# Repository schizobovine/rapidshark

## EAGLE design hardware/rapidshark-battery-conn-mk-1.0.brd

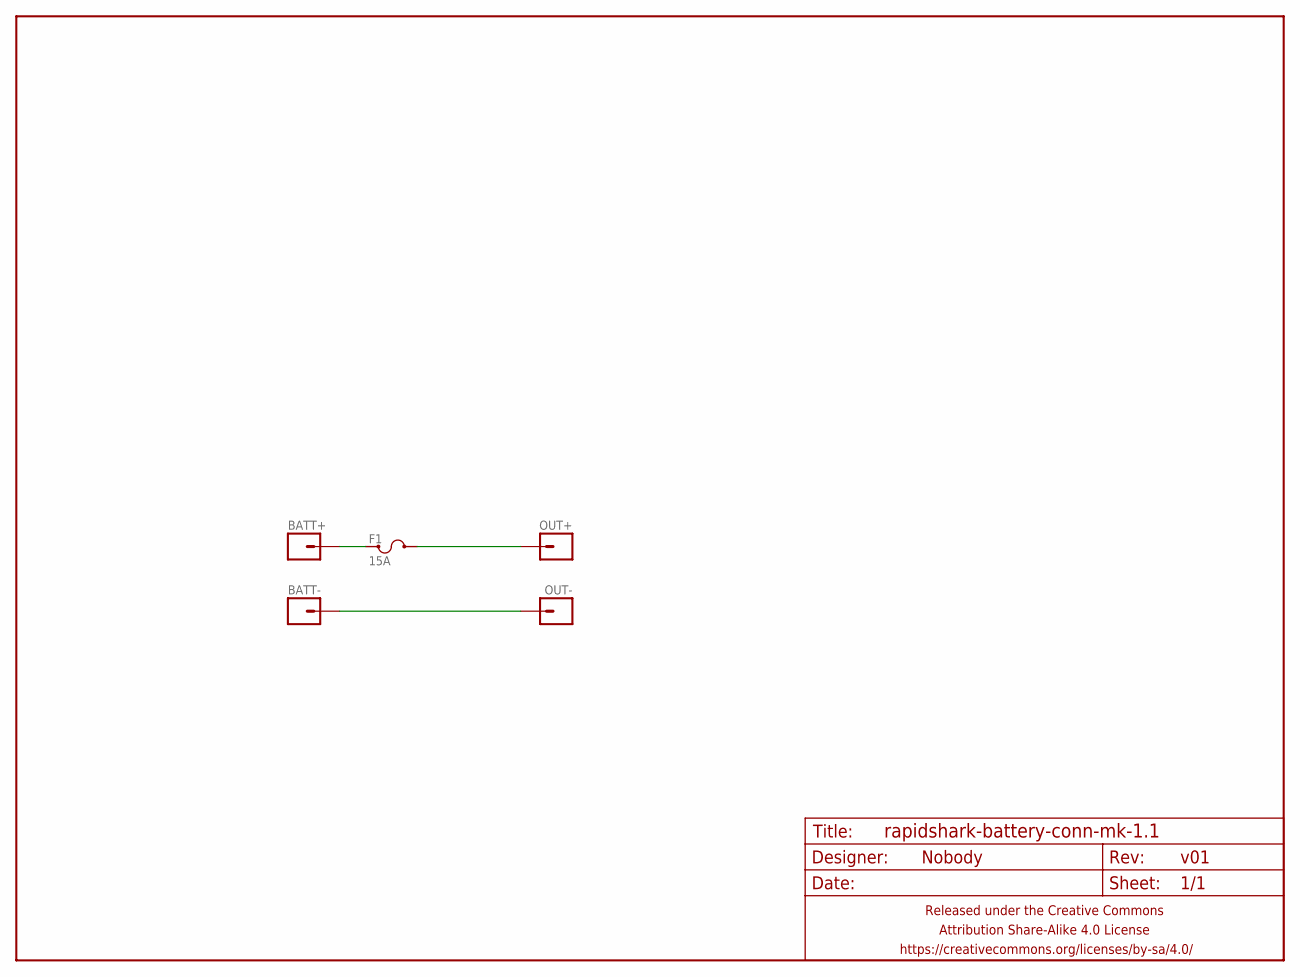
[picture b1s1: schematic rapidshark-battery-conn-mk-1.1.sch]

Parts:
BATT+: M01PTH-2.3MM; 1X01-2.3MM
BATT-: M01PTH-2.3MM; 1X01-2.3MM
F1: 15A; KEYSTONE-MINI-AUTO-FUSE-HOLDER
FRAME1: FRAME-LETTERNO_PACKAGE; DUMMY
OUT+: M0112AWG; 1X01-12AWG
OUT-: M0112AWG; 1X01-12AWG

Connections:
BATT+: BATT+.1, F1.P1@1 (1), F1.P1@2 (1)
BATT-: BATT-.1, OUT-.1
OUT+: F1.P2@1 (2), F1.P2@2 (2), OUT+.1

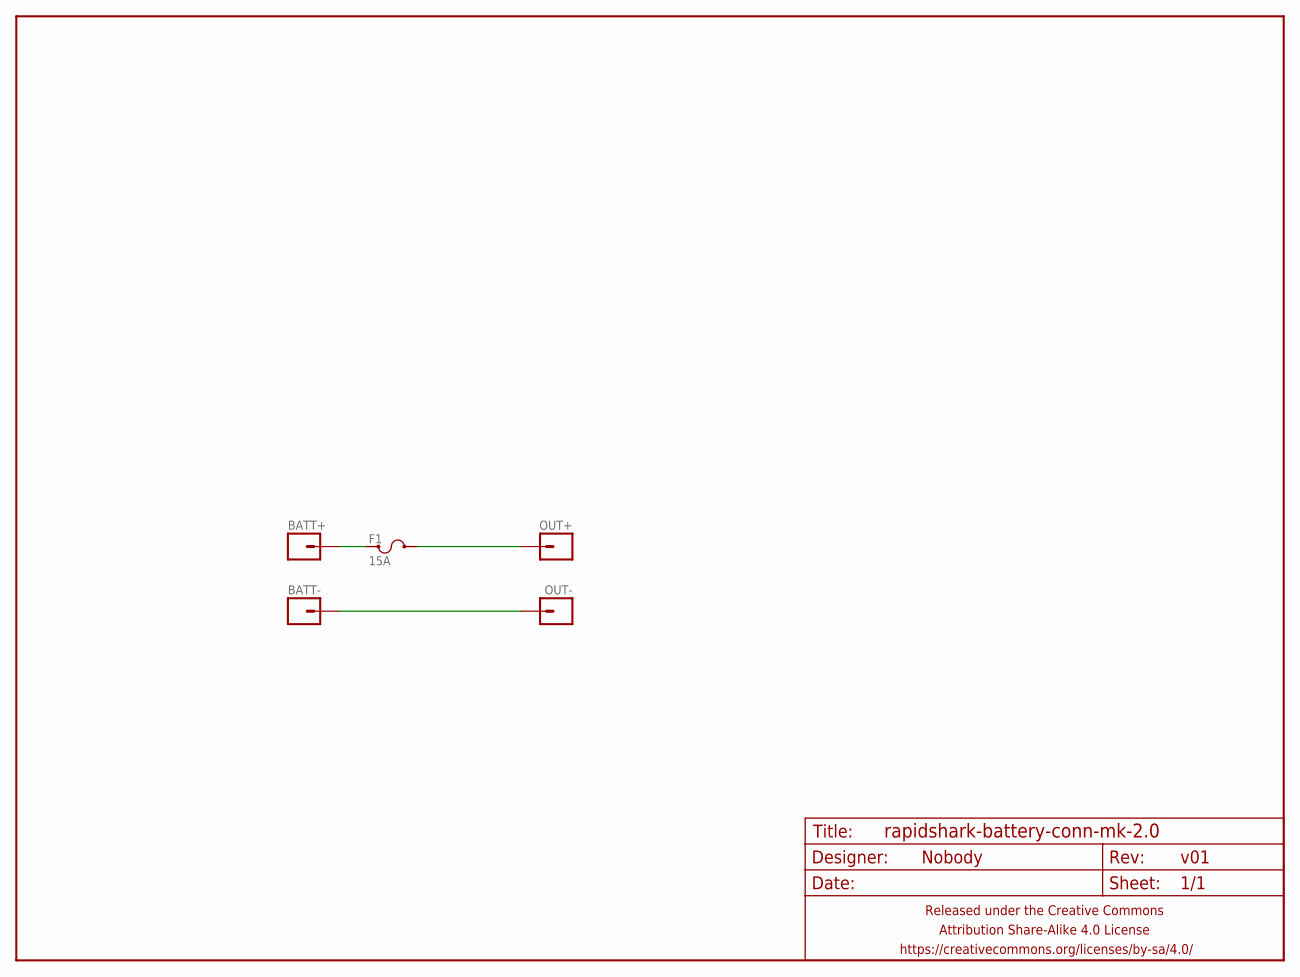
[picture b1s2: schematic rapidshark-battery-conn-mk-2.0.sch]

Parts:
BATT+: M01PTH-2.3MM; 1X01-2.3MM
BATT-: M01PTH-2.3MM; 1X01-2.3MM
F1: 15A; KEYSTONE-MINI-AUTO-FUSE-HOLDER
FRAME1: FRAME-LETTERNO_PACKAGE; DUMMY
OUT+: M0112AWG; 1X01-12AWG
OUT-: M0112AWG; 1X01-12AWG

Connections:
BATT+: BATT+.1, F1.P1@1 (1), F1.P1@2 (1)
BATT-: BATT-.1, OUT-.1
OUT+: F1.P2@1 (2), F1.P2@2 (2), OUT+.1

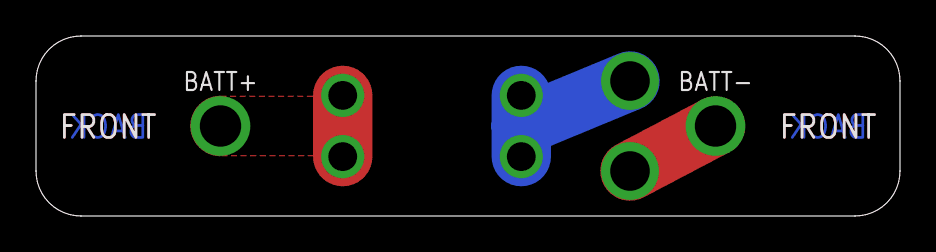
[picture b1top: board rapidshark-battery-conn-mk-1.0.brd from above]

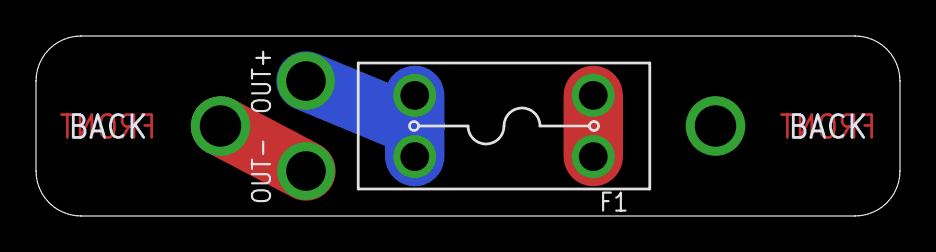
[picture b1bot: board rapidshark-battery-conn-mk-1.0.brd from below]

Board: 2 copper layers, 48.0 x 10.0 mm, 6 parts (3 on the bottom side), 3 nets.

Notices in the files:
parts and their libraries:
A_butts: Released under the Creative Commons Attribution Share-Alike 4.0 License
A_butts: https://creativecommons.org/licenses/by-sa/4.0
A_butts: Released under the Creative Commons
